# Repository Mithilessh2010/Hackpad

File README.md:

# Hackpad

## Overview
I made this for fun to help me open applications easier while streaming, the code is made to launch certain commands when ran so it can open up certain applications with just one click.

## Images / Showcase

### Overall Hackpad (Assembly)

### Schematic

### PCB

### Case and Fitment

## Bill of Materials (BOM)
- 1x printed bottom part  
- 1x printed top part  
- 1x XIAO-RP2040-DIP  
- 4x Cherry MX Switches  
- 2x SK6812 MINI LEDs
- Rotary Encoder

## Installation

```bash
git clone https://github.com/Mithilessh2010/Hackpad.git
cd Hackpad

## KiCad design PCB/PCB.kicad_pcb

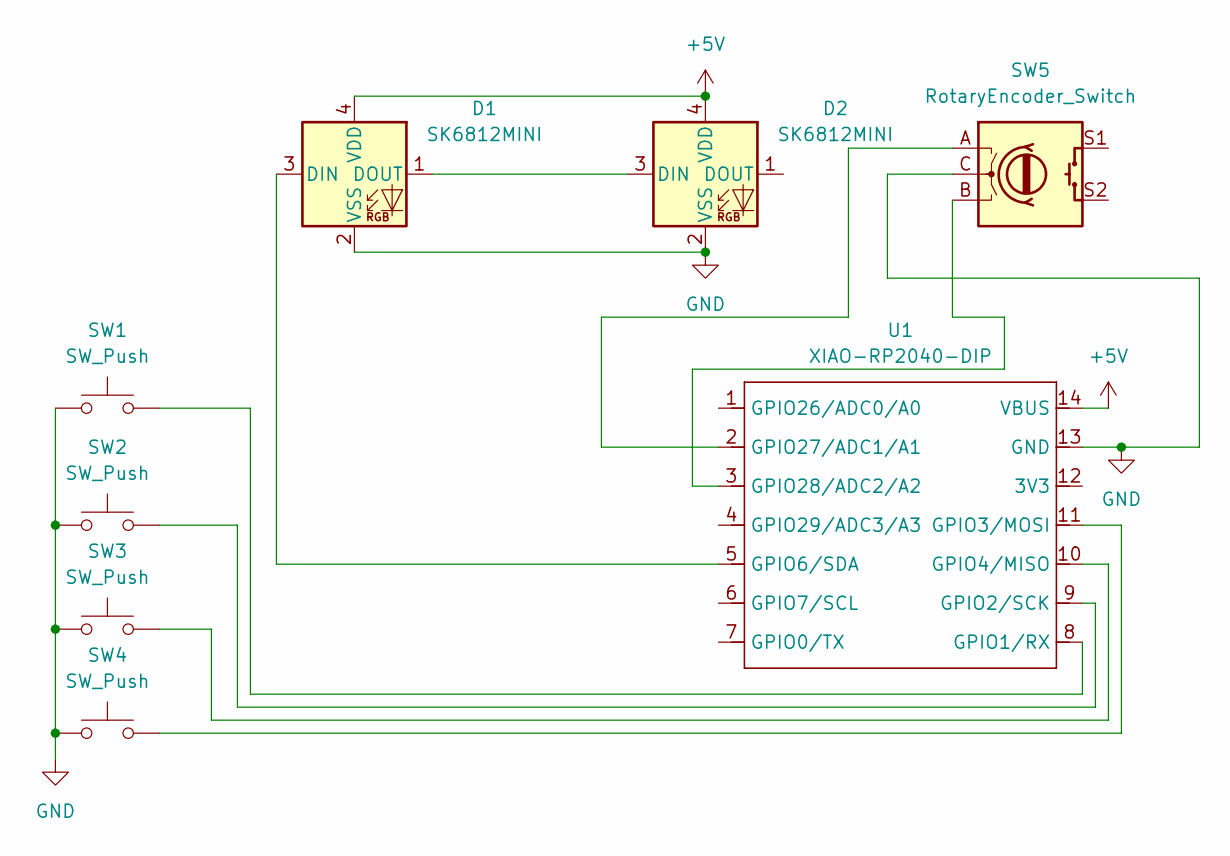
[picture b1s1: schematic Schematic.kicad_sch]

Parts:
D1, D2: SK6812MINI; LED_SK6812MINI_PLCC4_3.5x3.5mm_P1.75mm
SW1, SW2, SW3, SW4: SW_Push; SW_Cherry_MX_1.00u_PCB
SW5: RotaryEncoder_Switch; RotaryEncoder_Alps_EC11E-Switch_Vertical_H20mm
U1: XIAO-RP2040-DIP

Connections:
+5V: D1.4 (VDD), D2.4 (VDD), U1.14 (VBUS)
GND: D1.2 (VSS), D2.2 (VSS), SW1.1, SW2.1, SW3.1, SW4.1, SW5.C, U1.13 (GND)
unnamed: D1.3 (DIN), U1.5 (GPIO6/SDA)
unnamed: D1.1 (DOUT), D2.3 (DIN)
unnamed: SW1.2, U1.8 (GPIO1/RX)
unnamed: SW2.2, U1.9 (GPIO2/SCK)
unnamed: SW4.2, U1.11 (GPIO3/MOSI)
unnamed: SW3.2, U1.10 (GPIO4/MISO)
unnamed: SW5.A, U1.2 (GPIO27/ADC1/A1)
unnamed: SW5.B, U1.3 (GPIO28/ADC2/A2)

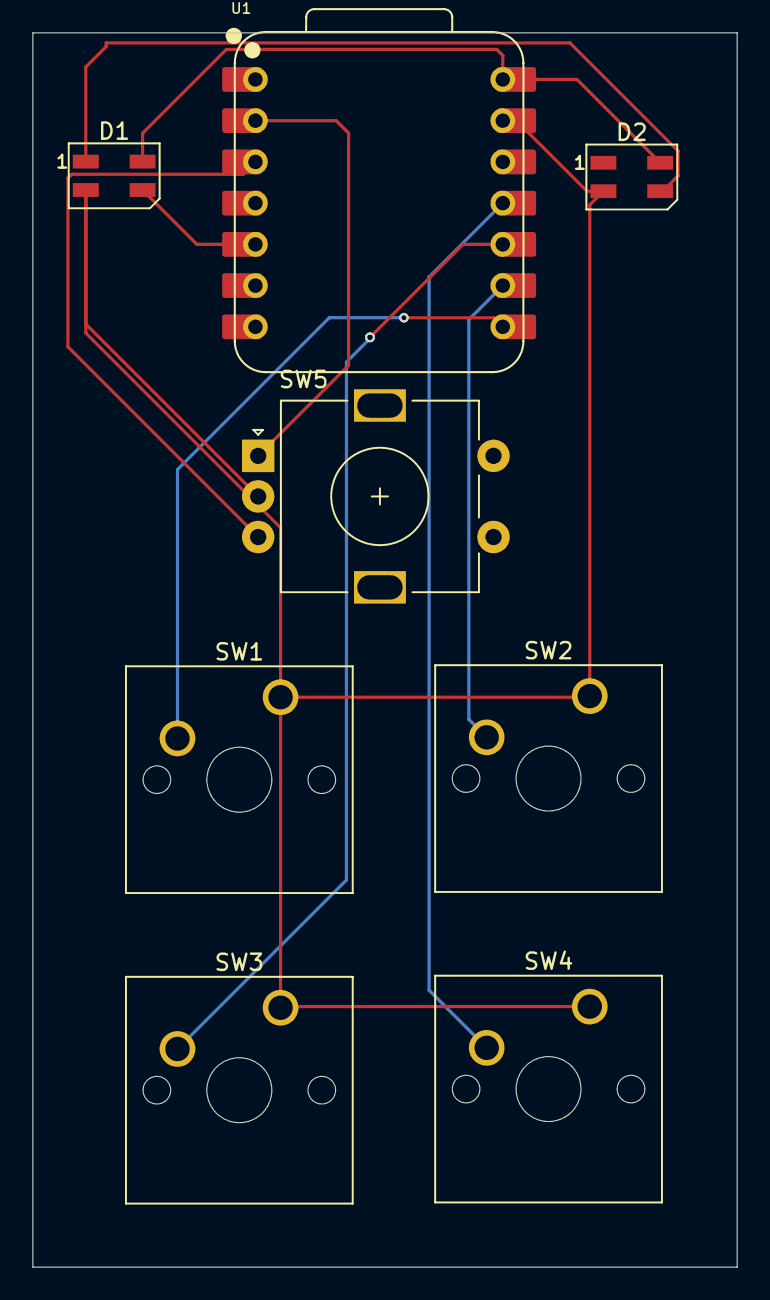
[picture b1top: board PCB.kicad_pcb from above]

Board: 2 copper layers, 43.4 x 76.0 mm, 8 parts (0 on the bottom side), 10 nets.

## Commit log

2025-11-30 Create README.md for Hackpad project
    Added README file with project overview, images, BOM, and installation instructions.
2025-11-30 Add firmware.py for keyboard functionality
2025-11-30 Replace key outputs with hotkey combos
    Updated keyboard keymap to include hotkey combinations for applications.
2025-11-30 Enhance README with project details and image updates
    Expanded the overview section to clarify the purpose of the project and updated image links for better accuracy.
2025-11-30 Fix image link for schematic in README
2025-11-30 Implement rotary encoder functionality
    Added rotary encoder support with volume control.
2025-11-30 Rename Cad ss.png to Cad.png
2025-11-30 Rename Screen Shot 2025-11-30 at 2.52.59 PM.png to Cad ss
2025-11-30 Rename Cad ss to Cad ss.png
